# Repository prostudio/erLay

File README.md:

erLay is a ultra-portable CoreXY 3D printer made by [Evan Yu](https://evanyu.dev) and [Aaron Huang](https://runthebot.me)

This printer is built to print small parts needed fast at robotics competitions where our main limitations are space and time. This printer will mainly print spacers, shaft collars, pullies, etc.

## [BOM](https://docs.google.com/spreadsheets/d/1s7m9KlAu-EawWQ5k7trbtZSsV5alHb0_lQaYVRcTUCk/view) | [CAD](https://cad.onshape.com/documents/c8077fee67b983eb99774ac1/w/a53d436f84abc79ea5797123/e/d46022eb7d51b7e61800c962?renderMode=0&uiState=67f3385f421ce1387ca2ed81) | [Journal](https://github.com/Badbird5907/erLay/blob/master/journal.md)

# Goals (we didn't manage to hit all of these within budget)
- Ultra-portable (for robotics competitions!!)
- Pico MMU (Optional) (Not in budget 😭)
- Zero Click ABL (Optional)
- Built-in carrying case (The printer will collapse into something like a pelican case) (Gave up on this one. see journal)
- Can be powered by a (multiple) power banks (Gave up on this one)
- NO STANDARD EXTRUSION (I think they look ewww and too normal)

# Features (Items in the final build)
- Locally sourced frame (Proudly Canadian)
- Easy to disassemble (8 Bolts)
- Core XY
- Klipper
- NeoPixel LEDs

# Interesting note on design!
As you will notice, most of the frame is built out of linear rods. I was inspired by hex shafts in FRC and how we tap them and use a bolt to clamp both sides. I decided to do this for infill to maximize rigidity and minimize construction/deconstruction time.

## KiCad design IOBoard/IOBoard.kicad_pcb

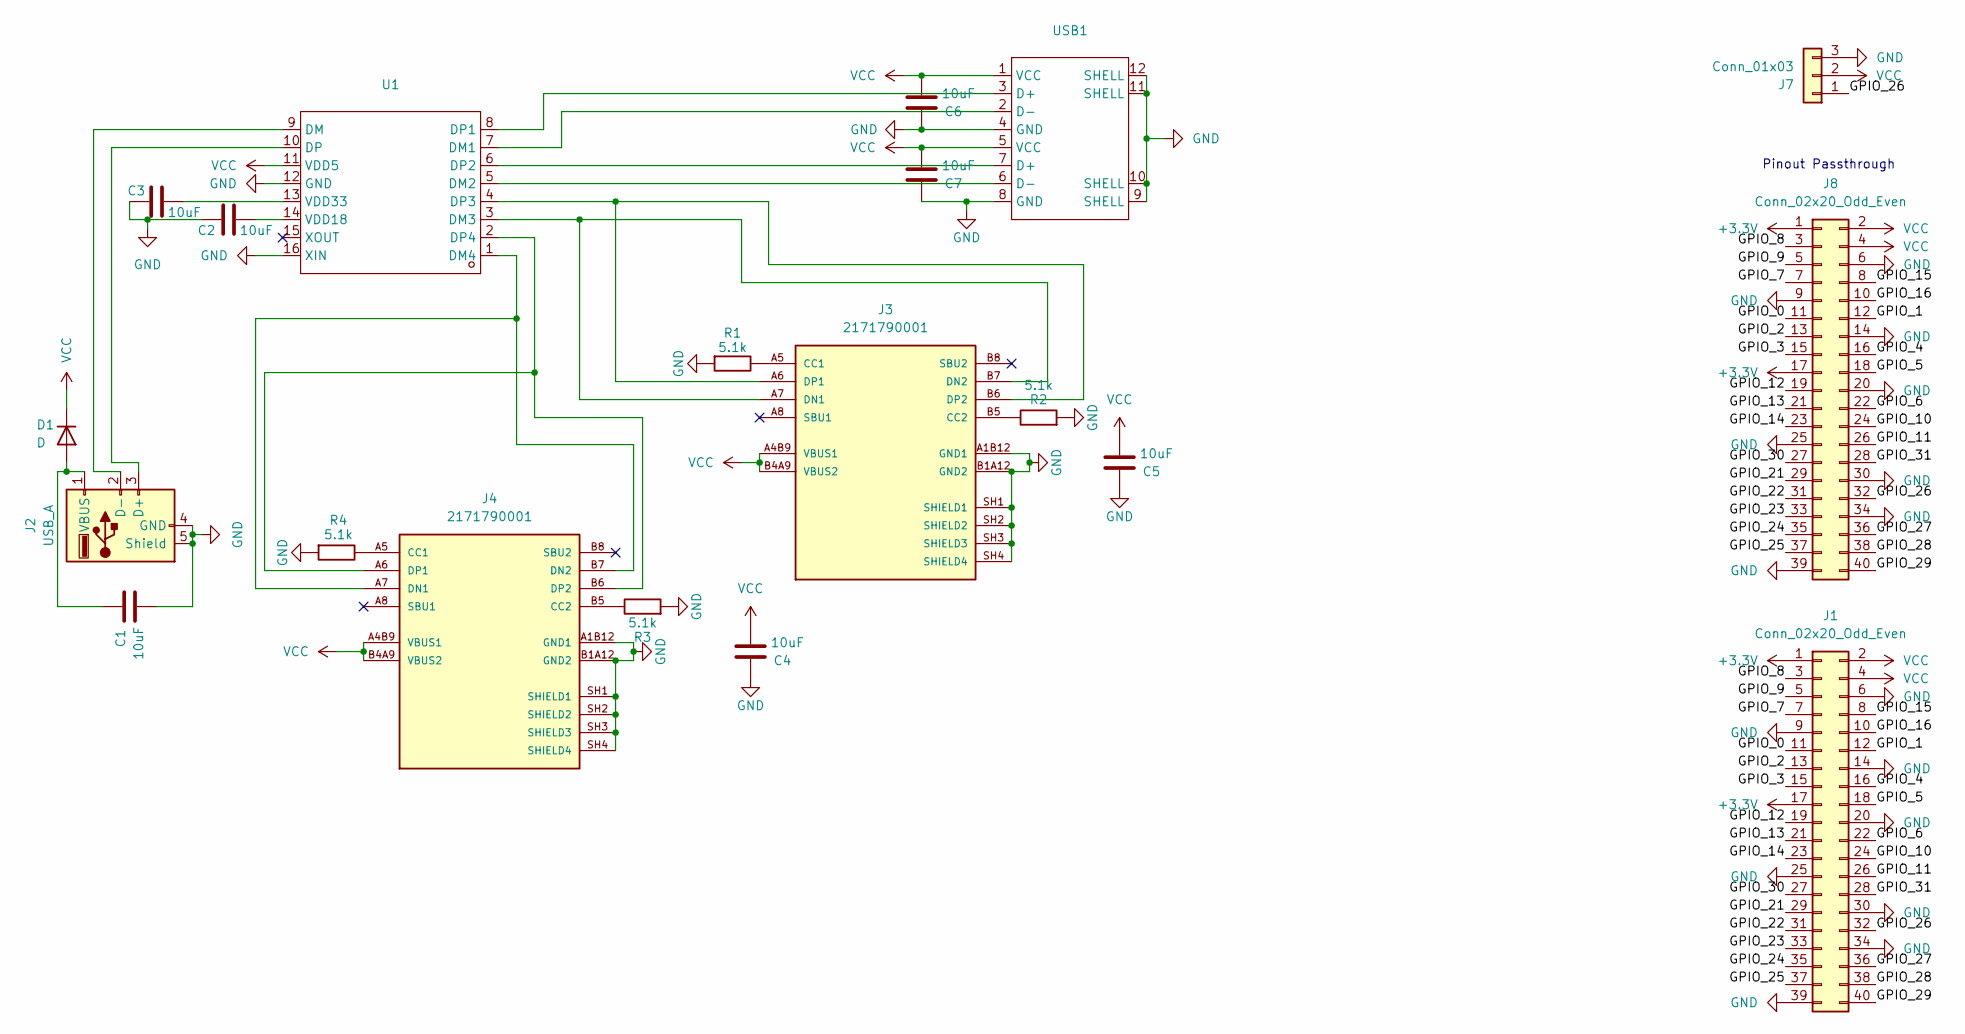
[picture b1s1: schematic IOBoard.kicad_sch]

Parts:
C1, C2, C3, C4, C5, C6, C7: 10uF; C_0603_1608Metric
D1: D; D_SOD-323
J1, J8: Conn_02x20_Odd_Even; PinHeader_2x20_P2.54mm_Vertical
J2: USB_A; USB-A-TH_USB-231-ARY
J3, J4: 2171790001; MOLEX_2171790001; PARTREV A1
J7: Conn_01x03; PinHeader_1x03_P2.54mm_Vertical
R1, R2, R3, R4: 5.1k; R_0603_1608Metric
U1: SL2.1A; Manufacturer Part SL2.1A; LCSC Part Name USB2.0高速4端口HUB控制器
USB1: USB-A-TH_AF-SS-JB17.6; Manufacturer Part AF SS-JB17.6; LCSC Part Name Type-A 母 弯插

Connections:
+3.3V: J1.1, J1.17, J8.1, J8.17
/GPIO_0: J1.11, J8.11
/GPIO_1: J1.12, J8.12
/GPIO_2: J1.13, J8.13
/GPIO_3: J1.15, J8.15
/GPIO_4: J1.16, J8.16
/GPIO_5: J1.18, J8.18
/GPIO_6: J1.22, J8.22
/GPIO_7: J1.7, J8.7
/GPIO_8: J1.3, J8.3
/GPIO_9: J1.5, J8.5
/GPIO_10: J1.24, J8.24
/GPIO_11: J1.26, J8.26
/GPIO_12: J1.19, J8.19
/GPIO_13: J1.21, J8.21
/GPIO_14: J1.23, J8.23
/GPIO_15: J1.8, J8.8
/GPIO_16: J1.10, J8.10
/GPIO_21: J1.29, J8.29
/GPIO_22: J1.31, J8.31
/GPIO_23: J1.33, J8.33
/GPIO_24: J1.35, J8.35
/GPIO_25: J1.37, J8.37
/GPIO_26: J1.32, J7.1, J8.32
/GPIO_27: J1.36, J8.36
/GPIO_28: J1.38, J8.38
/GPIO_29: J1.40, J8.40
/GPIO_30: J1.27, J8.27
/GPIO_31: J1.28, J8.28
GND: C1.2, C2.1, C3.1, C4.1, C5.1, C6.1, C7.1, J1.6, J1.9, J1.14, J1.20, J1.25, J1.30, J1.34, J1.39, J2.4 (GND), J2.5 (Shield), J3.A1B12 (GND1), J3.B1A12 (GND2), J3.SH1 (SHIELD1), J3.SH2 (SHIELD2), J3.SH3 (SHIELD3), J3.SH4 (SHIELD4), J4.A1B12 (GND1), J4.B1A12 (GND2), J4.SH1 (SHIELD1), J4.SH2 (SHIELD2), J4.SH3 (SHIELD3), J4.SH4 (SHIELD4), J7.3, J8.6, J8.9, J8.14, J8.20, J8.25, J8.30, J8.34, J8.39, R1.2, R2.2, R3.2, R4.2, U1.12 (GND), U1.16 (XIN), USB1.4 (GND), USB1.8 (GND), USB1.9 (SHELL), USB1.10 (SHELL), USB1.11 (SHELL), USB1.12 (SHELL)
unnamed: C1.1, D1.2 (A), J2.1 (VBUS)
unnamed: J2.3 (D+), U1.10 (DP)
unnamed: J2.2 (D-), U1.9 (DM)
unnamed: J3.A5 (CC1), R1.1
unnamed: J3.B5 (CC2), R2.1
unnamed: J3.A7 (DN1), J3.B7 (DN2), U1.3 (DM3)
unnamed: J3.A6 (DP1), J3.B6 (DP2), U1.4 (DP3)
unnamed: J4.A5 (CC1), R4.1
unnamed: J4.B5 (CC2), R3.1
unnamed: J4.A7 (DN1), J4.B7 (DN2), U1.1 (DM4)
unnamed: J4.A6 (DP1), J4.B6 (DP2), U1.2 (DP4)
unnamed: U1.7 (DM1), USB1.2 (D-)
unnamed: U1.5 (DM2), USB1.6 (D-)
unnamed: U1.8 (DP1), USB1.3 (D+)
unnamed: U1.6 (DP2), USB1.7 (D+)
unnamed: C2.2, U1.14 (VDD18)
unnamed: C3.2, U1.13 (VDD33)
VCC: C4.2, C5.2, C6.2, C7.2, D1.1 (K), J1.2, J1.4, J3.A4B9 (VBUS1), J3.B4A9 (VBUS2), J4.A4B9 (VBUS1), J4.B4A9 (VBUS2), J7.2, J8.2, J8.4, U1.11 (VDD5), USB1.1 (VCC), USB1.5 (VCC)

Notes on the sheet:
Pinout Passthrough

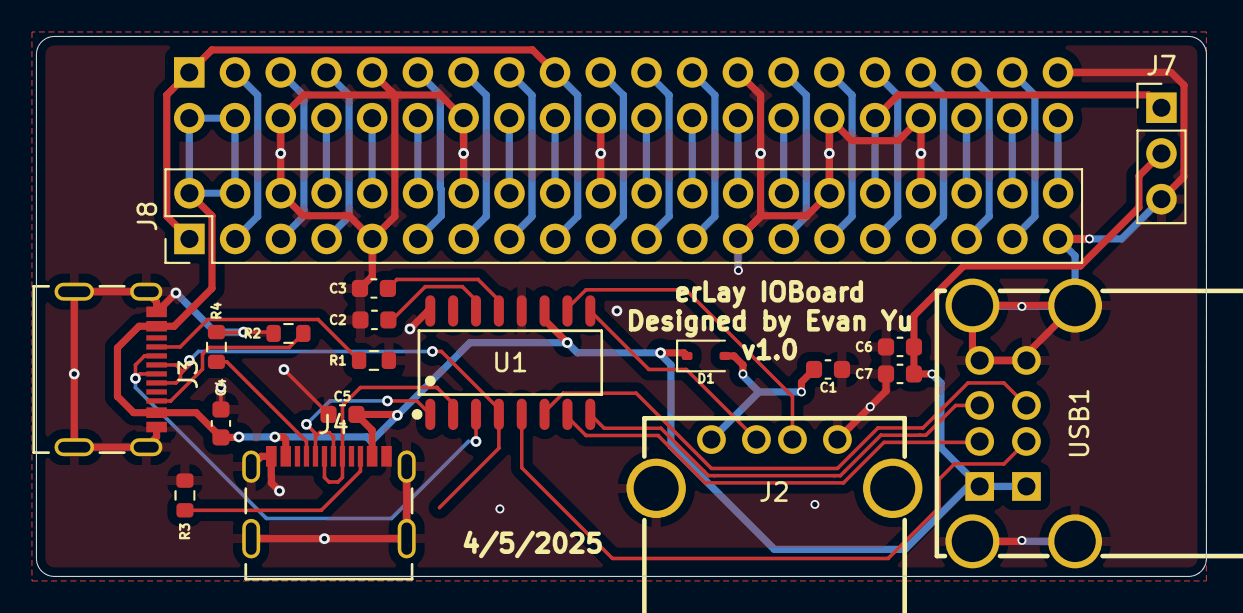
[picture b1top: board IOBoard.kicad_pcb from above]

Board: 2 copper layers, 65.0 x 30.0 mm, 20 parts (1 on the bottom side), 48 nets.

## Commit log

2025-02-13 we're ultra portable now
2025-02-14 I did something
2025-02-15 Log 14th and 15th
2025-02-18 feb 17 2025 evan
2025-02-18 bump hours
2025-02-23 Update goals
2025-02-23 feat: automatically update total time
2025-02-23 fix: add github token
2025-02-23 chore: update total time
2025-04-02 i want to kms
2025-04-05 Initialize IOBoard kicad project
2025-04-05 complete schematic for usb hub
2025-04-06 feat: complete IOBoard
2025-04-06 add PDSU as a git submodule (development still paused)
2025-04-07 optimize pcb (yesterday)
2025-04-07 we're done!
2025-04-07 chore: move log to journal.md
2025-04-07 add journal link and clean up readme
2025-04-07 update journal
2025-04-07 crashout
2025-04-07 asdkjahsfk
2025-04-12 Update IOBoard usb c connectors
